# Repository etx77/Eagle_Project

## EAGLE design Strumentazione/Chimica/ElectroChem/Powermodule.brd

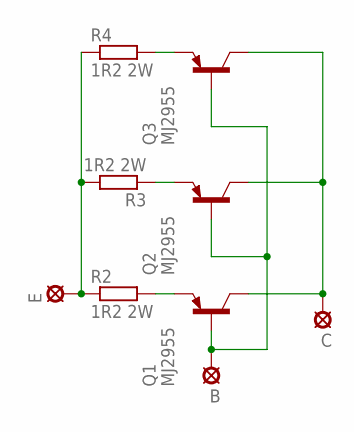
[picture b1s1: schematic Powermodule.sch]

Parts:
B: SE14
C: SE14
E: SE14
Q1, Q2, Q3: MJ2955; TO3
R2, R3, R4: 1R2 2W; 0207/10

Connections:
unnamed: E.MP, R2.1, R3.2, R4.1
unnamed: Q3.E, R4.2
unnamed: Q2.E, R3.1
unnamed: Q1.E, R2.2
unnamed: C.MP, Q1.C, Q1.C/ (C), Q2.C, Q2.C/ (C), Q3.C, Q3.C/ (C)
unnamed: B.MP, Q1.B, Q2.B, Q3.B

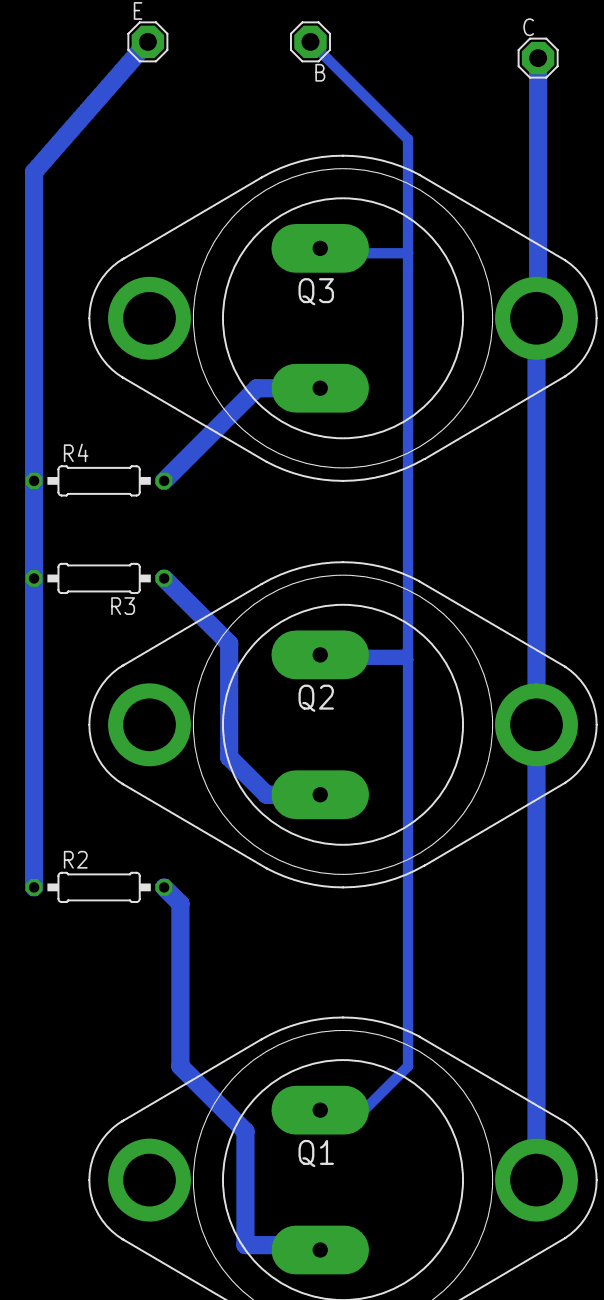
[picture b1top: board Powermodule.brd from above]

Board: 2 copper layers, 9 parts (0 on the bottom side), 6 nets.

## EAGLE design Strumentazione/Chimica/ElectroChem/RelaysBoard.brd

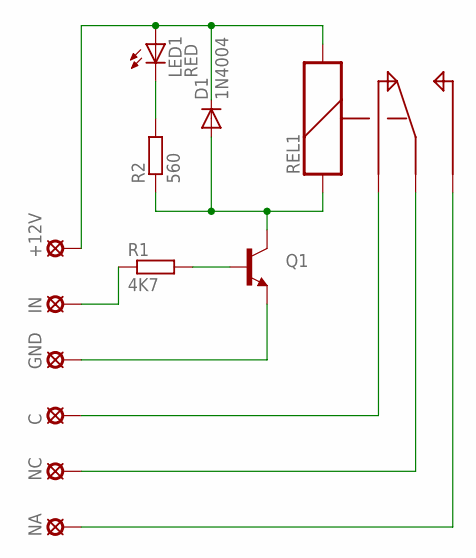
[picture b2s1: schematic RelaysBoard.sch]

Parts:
+12V: LSP10
C: LSP10
D1: 1N4004; DO41-10
GND: LSP10
IN: LSP10
LED1: RED; LED5MM
NA: LSP10
NC: LSP10
Q1: TRANSISTOR_NPNBC547; TO-92-AMMO
R1: 4K7; 0207/12
R2: 560; 0207/10
REL1: REL-5PIN

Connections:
unnamed: +12V.MP, D1.C, LED1.A, REL1.S2
unnamed: D1.A, Q1.1 (C), R2.1, REL1.S1
unnamed: Q1.2 (B), R1.2
unnamed: LED1.K (C), R2.2
unnamed: GND.MP, Q1.3 (E)
unnamed: C.MP, REL1.S
unnamed: NC.MP, REL1.C
unnamed: NA.MP, REL1.O
unnamed: IN.MP, R1.1

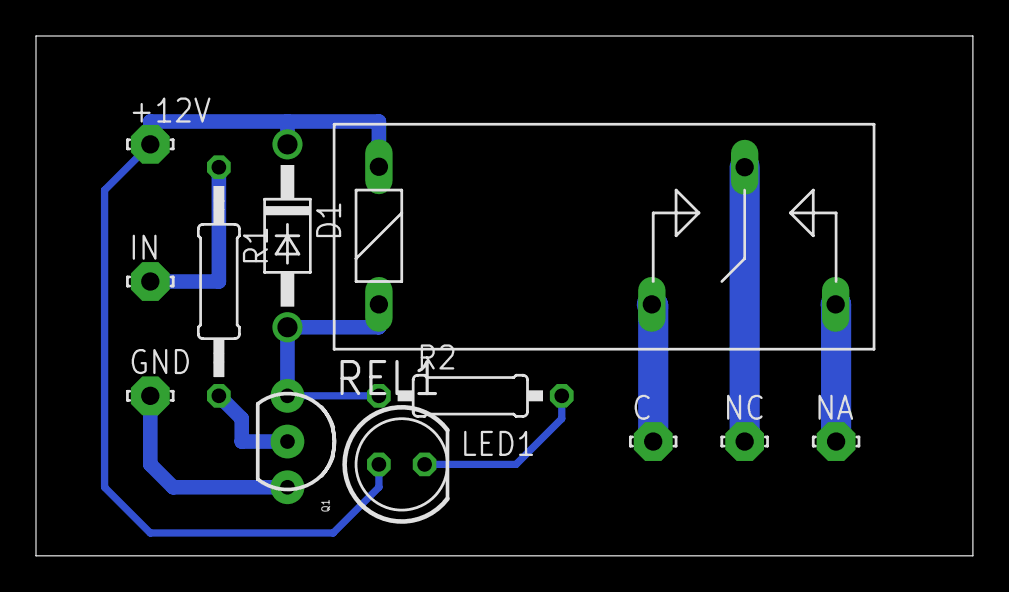
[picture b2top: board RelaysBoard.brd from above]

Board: 2 copper layers, 52.0 x 28.9 mm, 12 parts (0 on the bottom side), 9 nets.

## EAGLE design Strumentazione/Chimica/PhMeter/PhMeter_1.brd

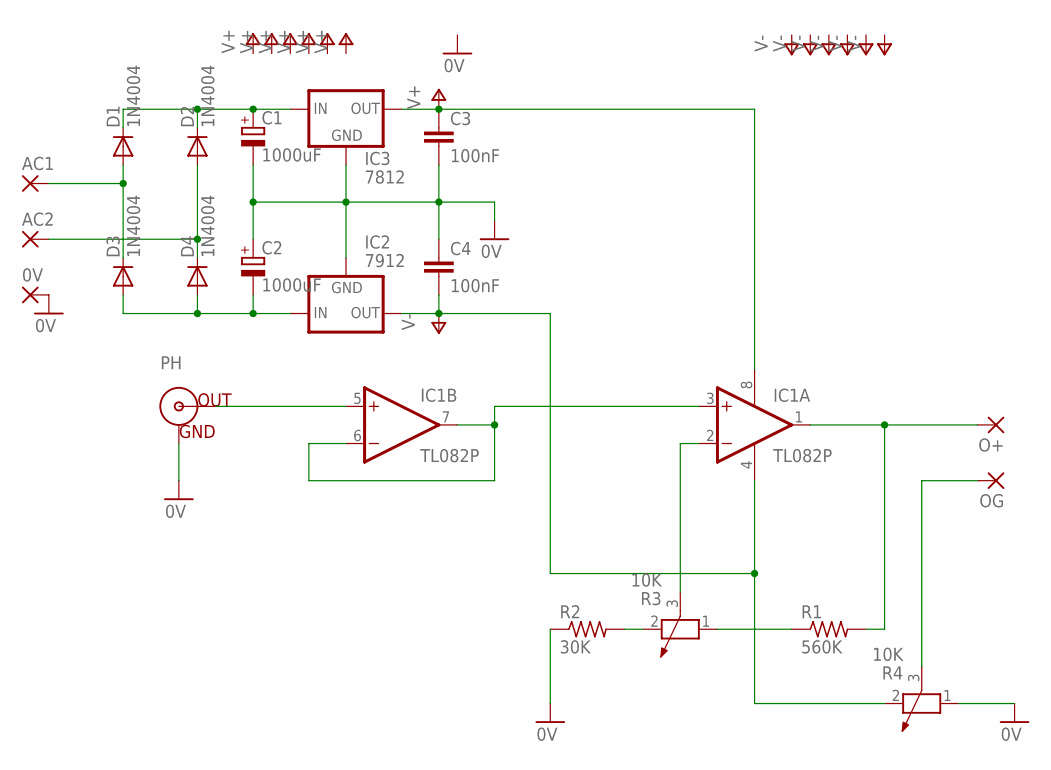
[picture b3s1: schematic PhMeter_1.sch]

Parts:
0V: 1,6/0,8
AC1, AC2: 1,6/0,8
C1, C2: 1000uF; E7,5-18
C3, C4: 100nF; C050-025X075
D1, D2, D3, D4: 1N4004; DO41-10
IC1: TL082P; DIL08
IC2: 7912; 79XXS
IC3: 7812; 78XXS
O+: 1,6/0,8
OG: 1,6/0,8
PH: BNCPTH; BNC
R1: 560K; 0207/10
R2: 30K; 0207/10
R3, R4: 10K; PT-10

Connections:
0V: 0V.1, C1.-, C2.+, C3.2, C4.1, IC2.GND, IC3.GND, PH.GND, R2.1, R4.1
AC1: AC1.1, D1.A, D3.C
unnamed: IC1.3 (+IN), IC1.6 (-IN), IC1.7 (OUT)
unnamed: R2.2, R3.2
unnamed: AC2.1, D2.A, D4.C
unnamed: C1.+, D1.C, D2.C, IC3.IN
unnamed: C2.-, D3.A, D4.A, IC2.IN
unnamed: R1.1, R3.1
unnamed: IC1.1 (OUT), O+.1, R1.2
unnamed: IC1.2 (-IN), R3.3
unnamed: OG.1, R4.3
unnamed: IC1.5 (+IN), PH.S (OUT)
V+: C3.1, IC1.8 (V+), IC3.OUT
V-: C4.2, IC1.4 (V-), IC2.OUT, R4.2

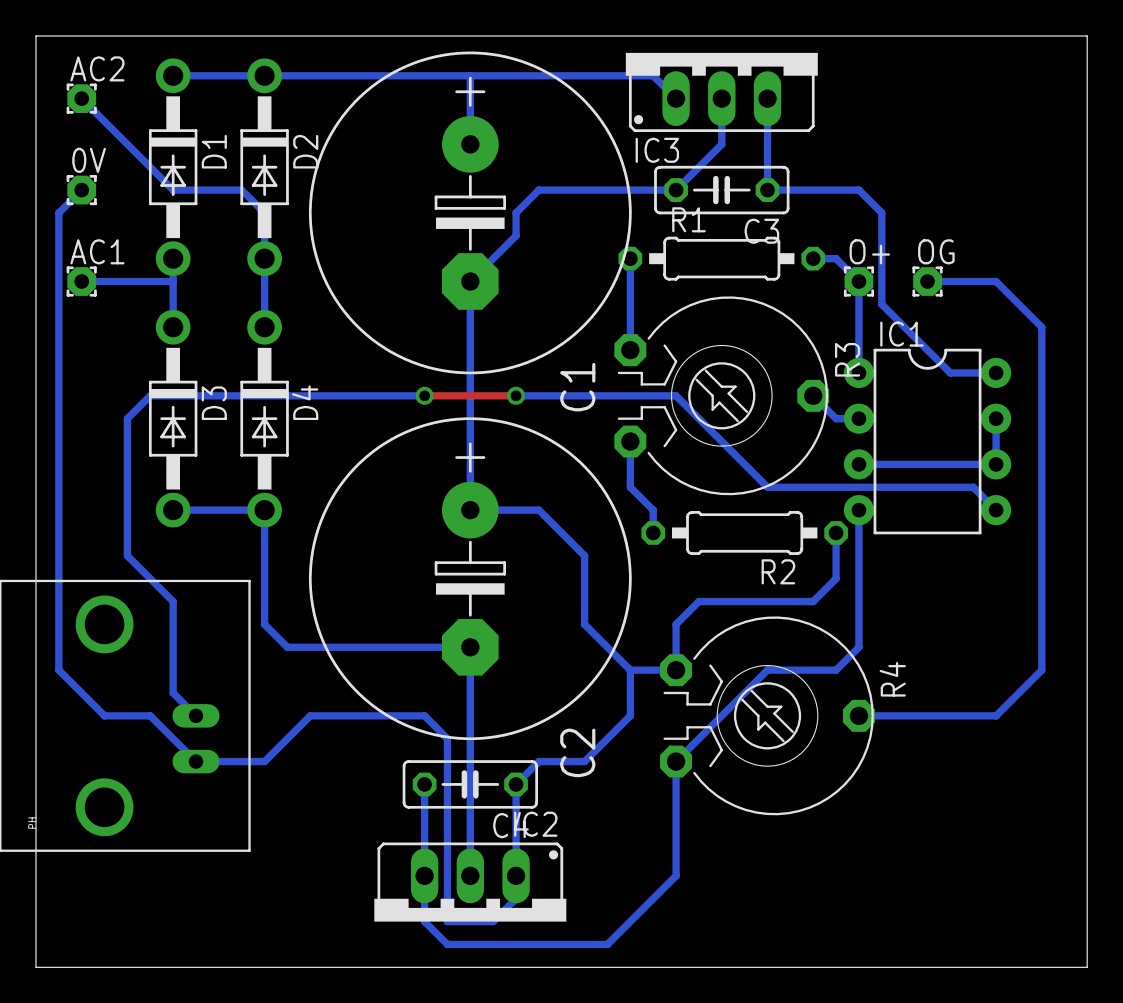
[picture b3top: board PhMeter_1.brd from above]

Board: 2 copper layers, 58.4 x 51.7 mm, 21 parts (0 on the bottom side), 14 nets.

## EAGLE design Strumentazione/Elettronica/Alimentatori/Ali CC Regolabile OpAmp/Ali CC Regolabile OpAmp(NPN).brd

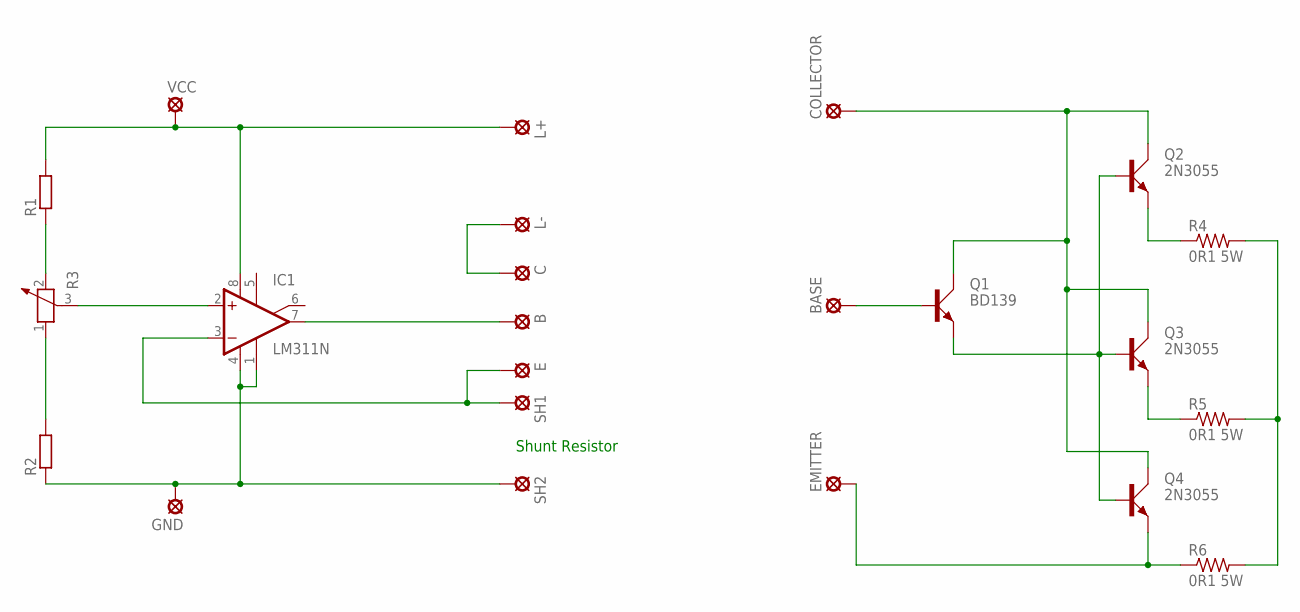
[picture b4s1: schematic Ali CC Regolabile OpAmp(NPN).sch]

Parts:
B: SE14
BASE: SE14
C: SE14
COLLECTOR: SE14
E: SE14
EMITTER: SE14
GND: SE14
IC1: LM311N; DIL08
L+: SE14
L-: SE14
Q1: BD139; TO126AV
Q2, Q3, Q4: 2N3055; TO3A
R1, R2: R-EU_0207/12; 0207/12
R3: POTENTIOMETER_PT-10; PT-10
R4, R5, R6: 0R1 5W; 0617/22
SH1, SH2: SE14
VCC: SE14

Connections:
unnamed: B.MP, IC1.7 (OUT)
unnamed: E.MP, IC1.3 (-IN), SH1.MP
unnamed: C.MP, L-.MP
unnamed: IC1.8 (V+), L+.MP, R1.2, VCC.MP
unnamed: R1.1, R3.2
unnamed: R2.2, R3.1
unnamed: IC1.2 (+IN), R3.3
unnamed: GND.MP, IC1.1 (GND), IC1.4 (V-), R2.1, SH2.MP
unnamed: Q3.E, R5.1
unnamed: EMITTER.MP, Q4.E, R6.1
unnamed: COLLECTOR.MP, Q1.C, Q2.C, Q2.C1 (C), Q3.C, Q3.C1 (C), Q4.C, Q4.C1 (C)
unnamed: Q2.E, R4.1
unnamed: R4.2, R5.2, R6.2
unnamed: Q1.E, Q2.B, Q3.B, Q4.B
unnamed: BASE.MP, Q1.B

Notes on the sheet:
Shunt Resistor

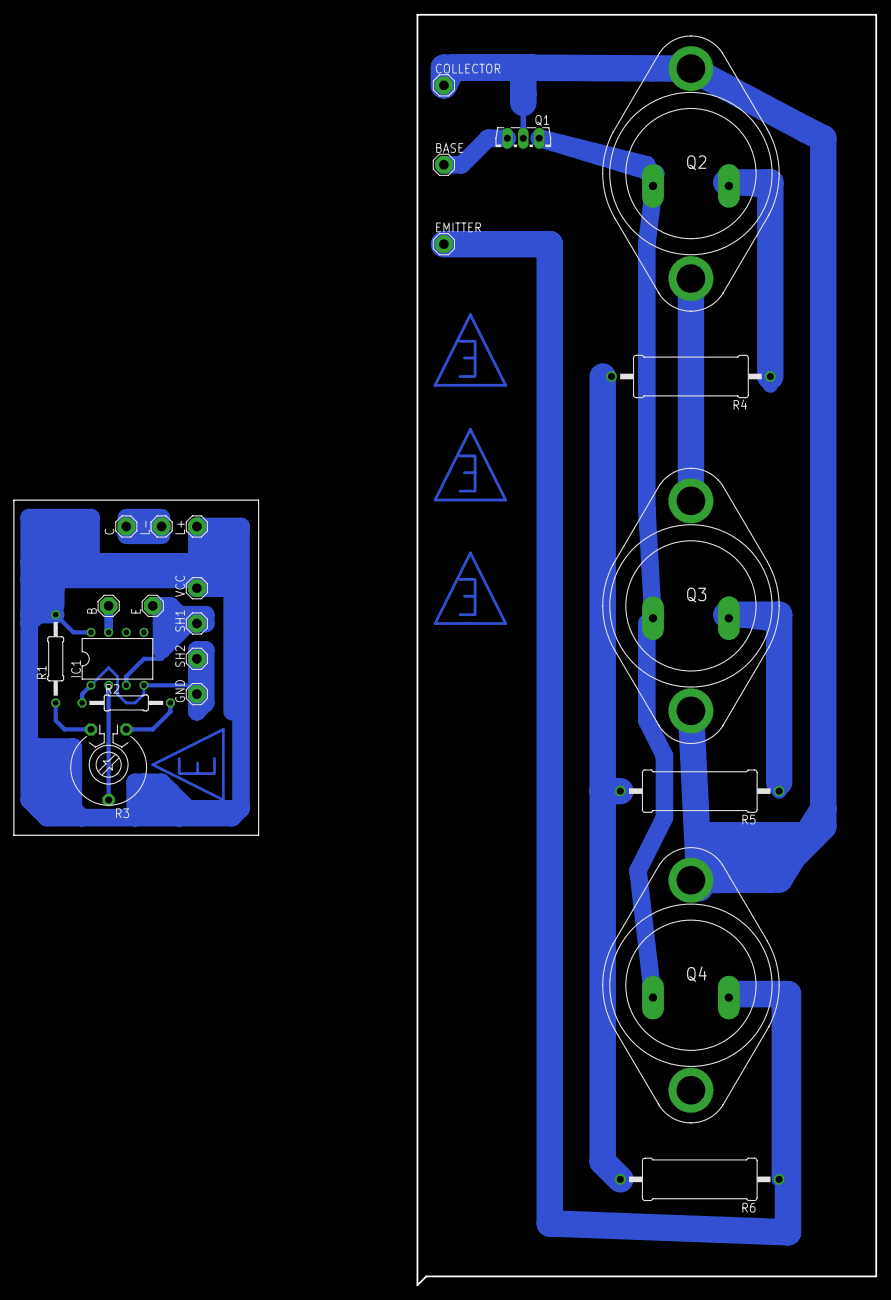
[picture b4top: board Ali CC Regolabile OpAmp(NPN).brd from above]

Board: 2 copper layers, 124.1 x 182.9 mm, 27 parts (0 on the bottom side), 15 nets.

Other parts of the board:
U$1, U$2, U$3, U$4: LOGO

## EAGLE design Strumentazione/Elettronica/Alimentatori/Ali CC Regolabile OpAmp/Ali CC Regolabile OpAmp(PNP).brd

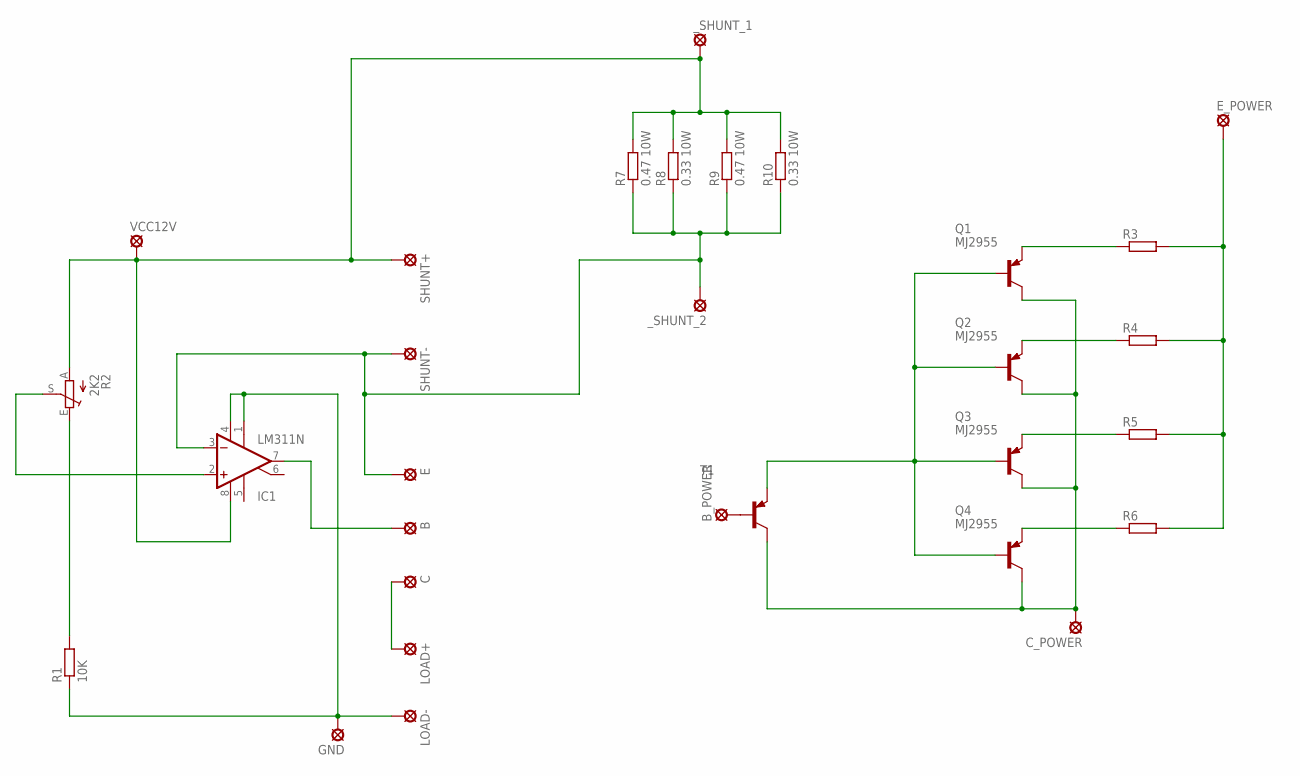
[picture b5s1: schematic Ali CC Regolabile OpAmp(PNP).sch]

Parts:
B: SE14
B_POWER: LSP10
C: SE14
C_POWER: LSP10
E: SE14
E_POWER: LSP10
GND: SE14
IC1: LM311N; DIL08
LOAD+: SE14
LOAD-: SE14
Q1, Q2, Q3, Q4: MJ2955; TO3
R1: 10K; 0207/15
R2: 2K2; CIP20C-6MM
R3, R4, R5, R6: R-EU_VTA53; VTA53
R7, R9: 0.47 10W; VTA53
R8, R10: 0.33 10W; VTA53
SHUNT+: SE14
SHUNT-: SE14
T1: BC558A-PNP-TO92-EBC; TO92-EBC
VCC12V: SE14
_SHUNT_1, _SHUNT_2: LSP10

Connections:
unnamed: E.MP, IC1.3 (-IN), R7.1, R8.1, R9.1, R10.1, SHUNT-.MP, _SHUNT_2.MP
unnamed: B.MP, IC1.7 (OUT)
unnamed: C.MP, LOAD+.MP
unnamed: GND.MP, IC1.1 (GND), IC1.4 (V-), LOAD-.MP, R1.1
unnamed: R1.2, R2.E
unnamed: Q1.E, R3.1
unnamed: IC1.2 (+IN), R2.S
unnamed: Q2.E, R4.1
unnamed: Q3.E, R5.1
unnamed: Q4.E, R6.1
unnamed: E_POWER.MP, R3.2, R4.2, R5.2, R6.2
unnamed: C_POWER.MP, Q1.C, Q1.C/ (C), Q2.C, Q2.C/ (C), Q3.C, Q3.C/ (C), Q4.C, Q4.C/ (C), T1.C
unnamed: Q1.B, Q2.B, Q3.B, Q4.B, T1.E
unnamed: B_POWER.MP, T1.B
unnamed: IC1.8 (V+), R2.A, R7.2, R8.2, R9.2, R10.2, SHUNT+.MP, VCC12V.MP, _SHUNT_1.MP

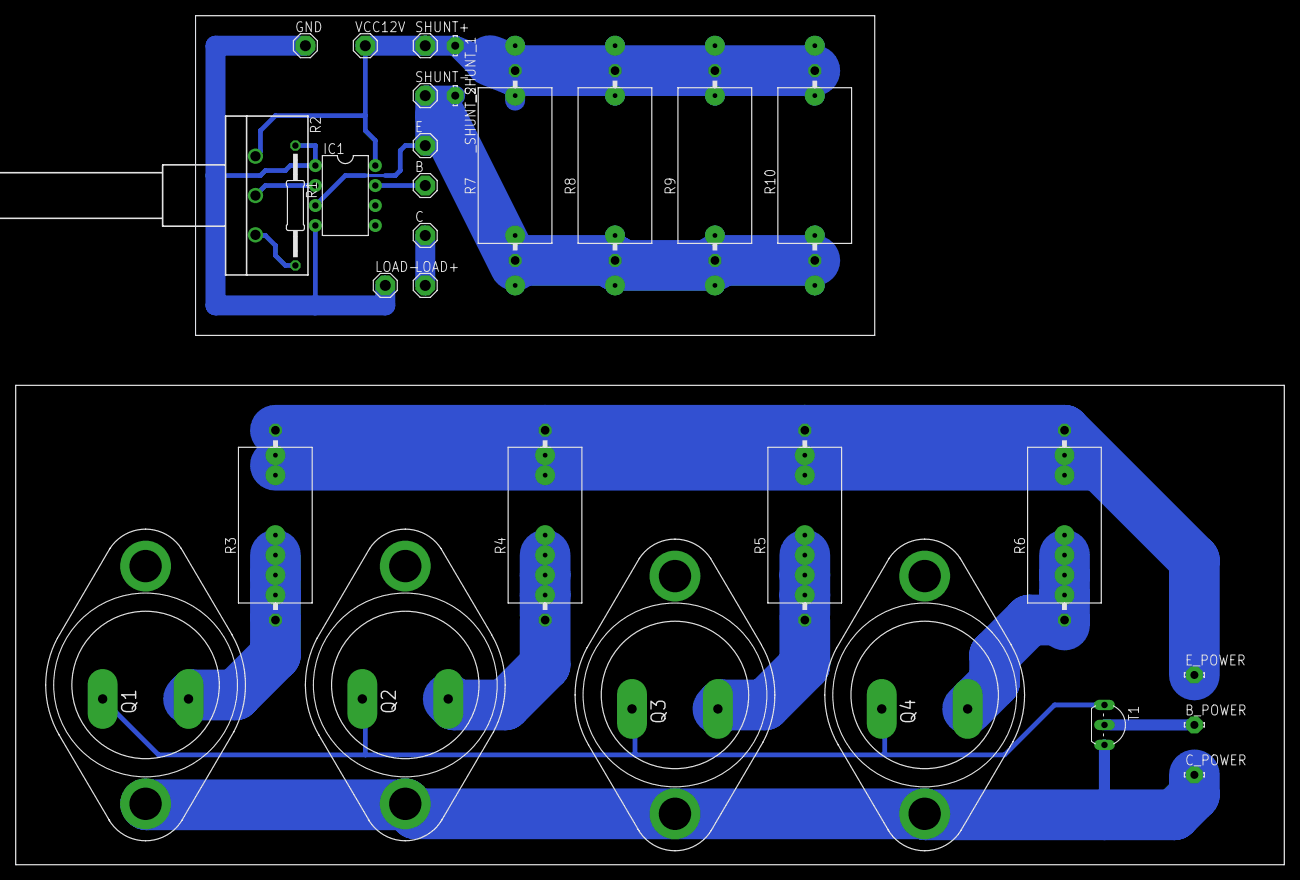
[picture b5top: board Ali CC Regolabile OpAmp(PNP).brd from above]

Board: 2 copper layers, 161.3 x 108.0 mm, 30 parts (0 on the bottom side), 15 nets.

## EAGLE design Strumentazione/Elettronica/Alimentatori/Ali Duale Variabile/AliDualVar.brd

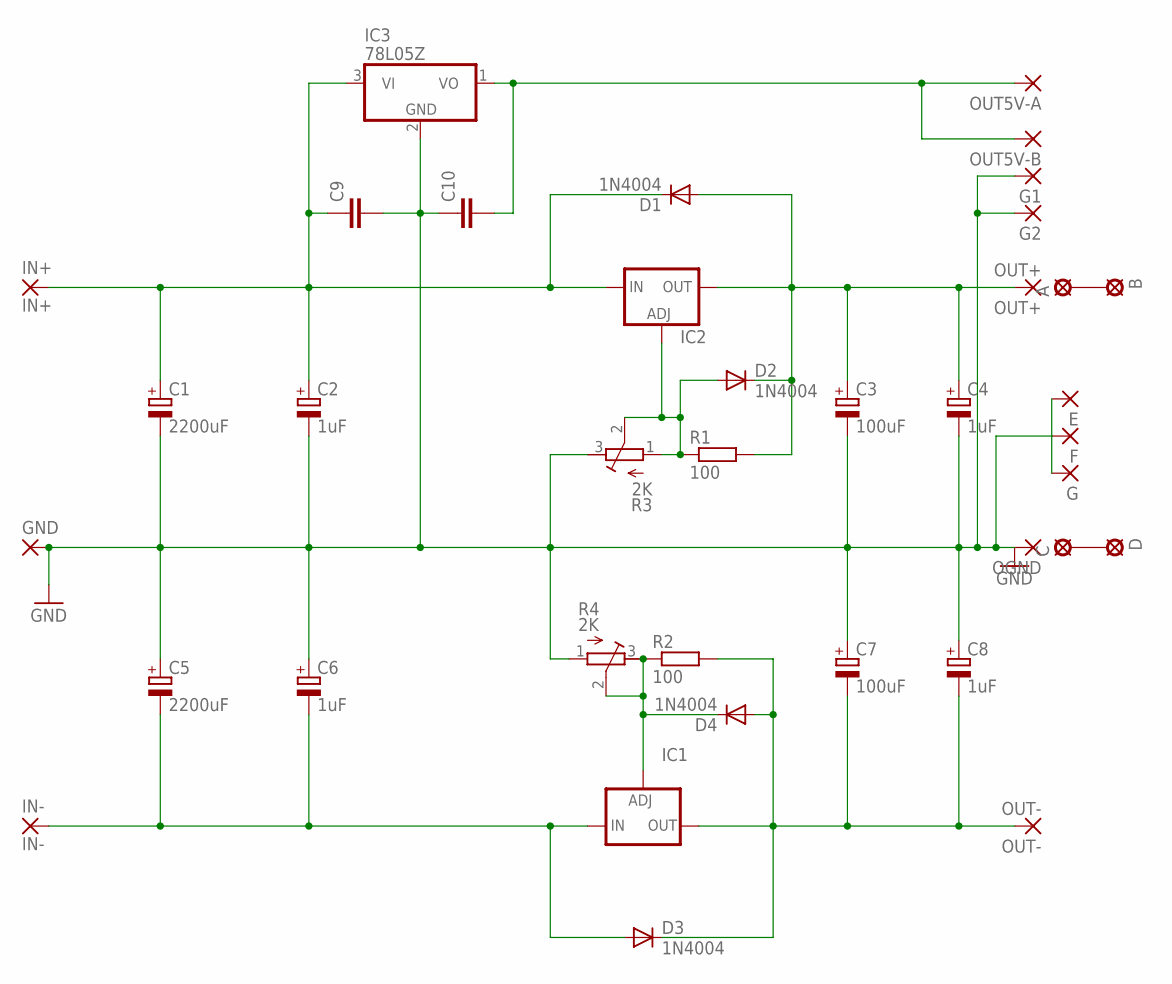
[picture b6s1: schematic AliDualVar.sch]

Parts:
A: MCS10B
B: MCS10B
C: MCS10B
C1, C5: 2200uF; EB35D
C2, C4, C6, C8: 1uF; E5-13
C3, C7: 100uF; E5-13
C9, C10: C-EU025-024X044; C025-024X044
D: MCS10B
D1, D2, D3, D4: 1N4004; DO41-10
E: 3,81/1,4
F: 3,81/1,4
G, G1, G2: 3,81/1,4
GND: 3,81/1,4
IC1: LM337TL; 337TL
IC2: LM317TL; 317TL
IC3: 78L05Z; TO92
IN+: IN+; 3,81/1,4
IN-: IN-; 3,81/1,4
OGND: 3,81/1,4
OUT5V-A, OUT5V-B: 3,81/1,4
OUT+: OUT+; 3,81/1,4
OUT-: OUT-; 3,81/1,4
R1, R2: 100; 0207/7
R3, R4: 2K; RTRIM3339P

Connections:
GND: C1.-, C2.-, C3.-, C4.-, C5.+, C6.+, C7.+, C8.+, C9.2, C10.1, E.1, F.1, G.1, G1.1, G2.1, GND.1, IC3.2 (GND), OGND.1, R3.3 (E), R4.1 (A)
unnamed: C3.+, C4.+, D1.A, D2.C, IC2.2 (OUT), OUT+.1, R1.2
unnamed: A.MP, B.MP
unnamed: C.MP, D.MP
unnamed: D2.A, IC2.1 (ADJ), R1.1, R3.1 (A), R3.2 (S)
unnamed: D4.C, IC1.1 (ADJ), R2.1, R4.2 (S), R4.3 (E)
unnamed: C7.-, C8.-, D3.C, D4.A, IC1.3 (OUT), OUT-.1, R2.2
unnamed: C5.-, C6.-, D3.A, IC1.2 (IN), IN-.1
unnamed: C10.2, IC3.1 (VO), OUT5V-A.1, OUT5V-B.1
unnamed: C1.+, C2.+, C9.1, D1.C, IC2.3 (IN), IC3.3 (VI), IN+.1

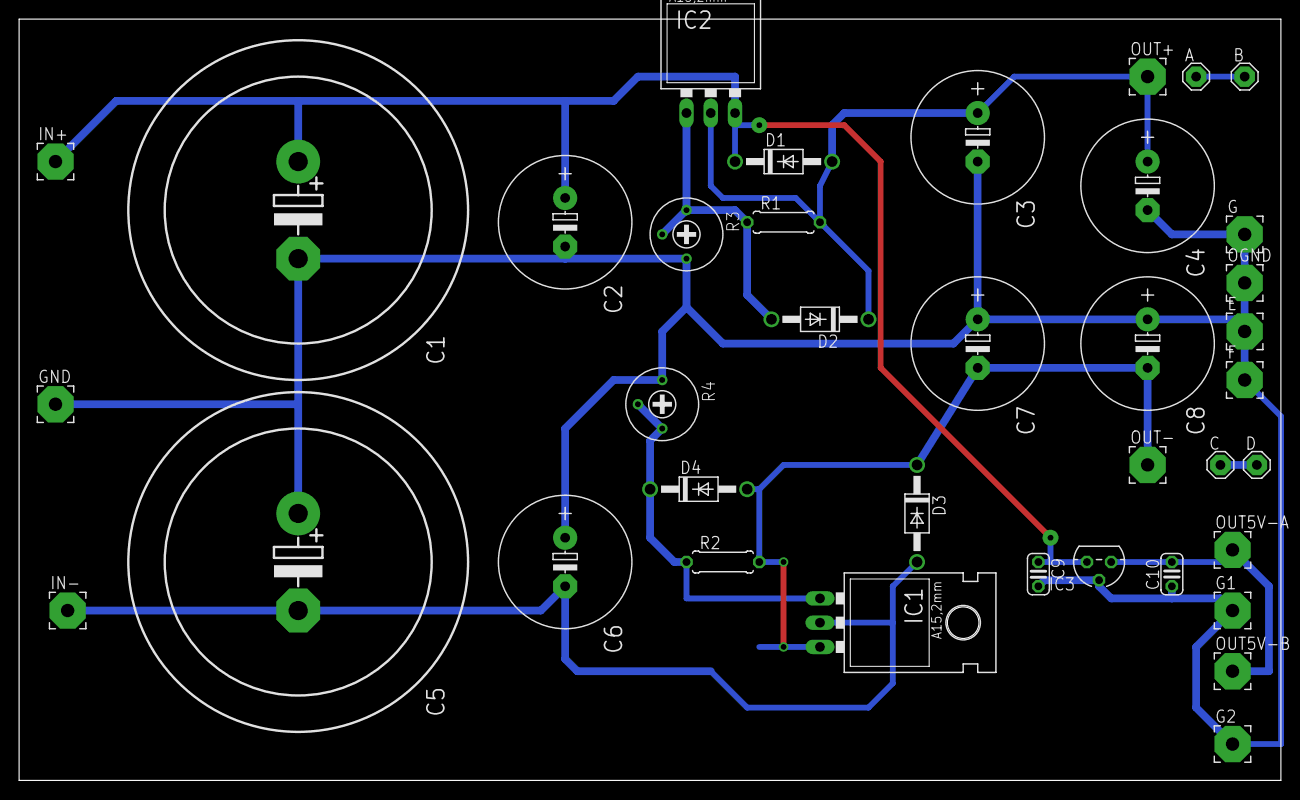
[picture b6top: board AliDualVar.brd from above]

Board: 2 copper layers, 132.1 x 79.7 mm, 38 parts (0 on the bottom side), 10 nets.

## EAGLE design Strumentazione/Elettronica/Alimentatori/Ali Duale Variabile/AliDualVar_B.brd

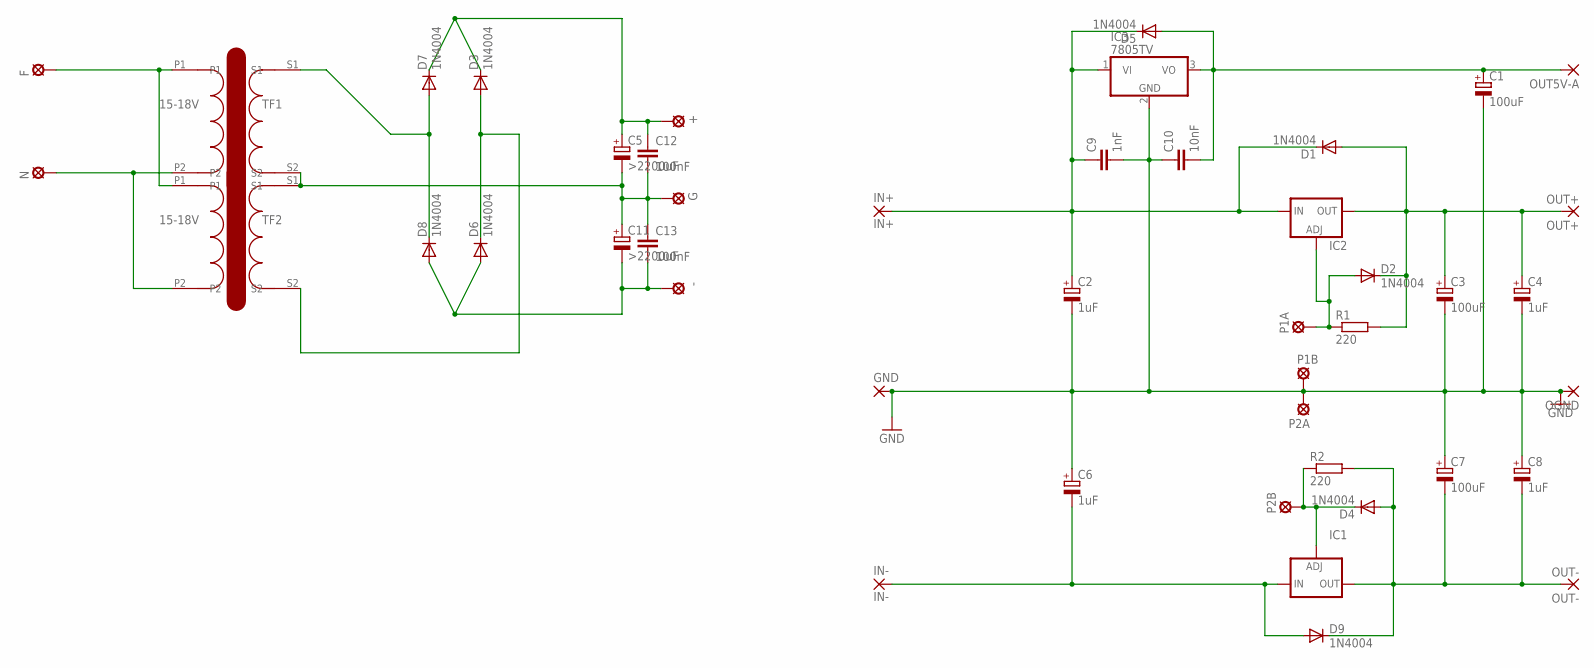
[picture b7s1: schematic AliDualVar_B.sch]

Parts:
+: LSP10
-: LSP10
C1, C3, C7: 100uF; E5-13
C2, C4, C6, C8: 1uF; E5-13
C5, C11: >2200uF; E7,5-16
C9: 1nF; C025-024X044
C10: 10nF; C025-024X044
C12, C13: 100nF; C050-035X075
D1, D2, D3, D4, D5, D6, D7, D8, D9: 1N4004; DO41-10
F: LSP10
G: LSP10
GND: 3,81/1,4
IC1: LM337TS; 337TS
IC2: LM317TS; 317TS
IC3: 7805TV; TO220V
IN+: IN+; 3,81/1,4
IN-: IN-; 3,81/1,4
N: LSP10
OGND: 3,81/1,4
OUT5V-A: 3,81/1,4
OUT+: OUT+; 3,81/1,4
OUT-: OUT-; 3,81/1,4
P1A, P1B, P2A, P2B: LSP10
R1, R2: 220; 0207/7
TF1, TF2: 15-18V; TRASFORMATORE_1_A

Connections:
GND: C1.-, C2.-, C3.-, C4.-, C6.+, C7.+, C8.+, C9.2, C10.1, GND.1, IC3.2 (GND), OGND.1, P1B.MP, P2A.MP
unnamed: C7.-, C8.-, D4.A, D9.C, IC1.3 (OUT), OUT-.1, R2.2
unnamed: C3.+, C4.+, D1.A, D2.C, IC2.2 (OUT), OUT+.1, R1.2
unnamed: F.MP, TF1.P1, TF2.P1
unnamed: C1.+, C10.2, D5.A, IC3.3 (VO), OUT5V-A.1
unnamed: D2.A, IC2.1 (ADJ), P1A.MP, R1.1
unnamed: D4.C, IC1.1 (ADJ), P2B.MP, R2.1
unnamed: D7.A, D8.C, TF1.S1
unnamed: C6.-, D9.A, IC1.2 (IN), IN-.1
unnamed: D3.A, D6.C, TF2.S2
unnamed: C2.+, C9.1, D1.C, D5.C, IC2.3 (IN), IC3.1 (VI), IN+.1
unnamed: +.MP, C5.+, C12.1, D3.C, D7.C
unnamed: N.MP, TF1.P2, TF2.P2
unnamed: C5.-, C11.+, C12.2, C13.1, G.MP, TF1.S2, TF2.S1
unnamed: -.MP, C11.-, C13.2, D6.A, D8.A

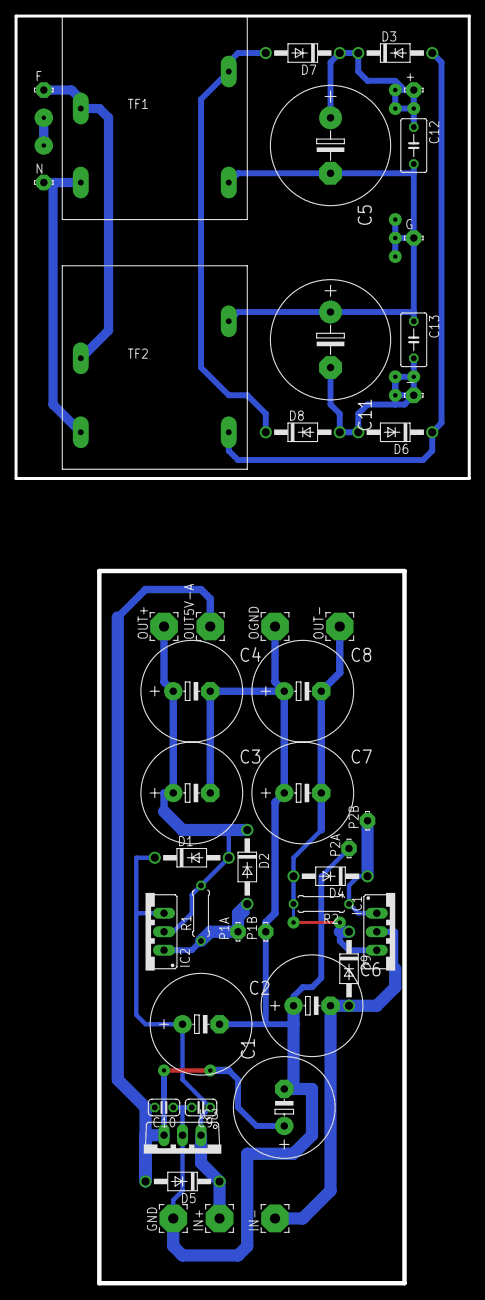
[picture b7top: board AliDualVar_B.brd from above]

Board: 2 copper layers, 62.2 x 174.0 mm, 45 parts (0 on the bottom side), 15 nets.

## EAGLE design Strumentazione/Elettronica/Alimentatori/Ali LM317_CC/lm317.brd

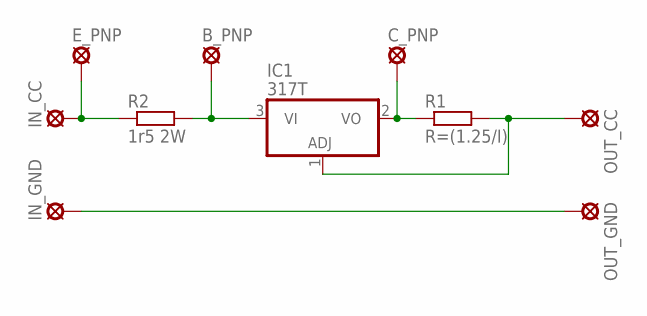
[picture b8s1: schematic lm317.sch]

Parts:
B_PNP: SE14
C_PNP: SE14
E_PNP: SE14
IC1: 317T; TO220H
IN_CC: SE14
IN_GND: SE14
OUT_CC: SE14
OUT_GND: SE14
R1: R=(1.25/I); 0617/22
R2: 1r5 2W; 0617/22

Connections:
unnamed: E_PNP.MP, IN_CC.MP, R2.1
unnamed: B_PNP.MP, IC1.3 (VI), R2.2
unnamed: C_PNP.MP, IC1.2 (VO), R1.1
unnamed: IC1.1 (ADJ), OUT_CC.MP, R1.2
unnamed: IN_GND.MP, OUT_GND.MP

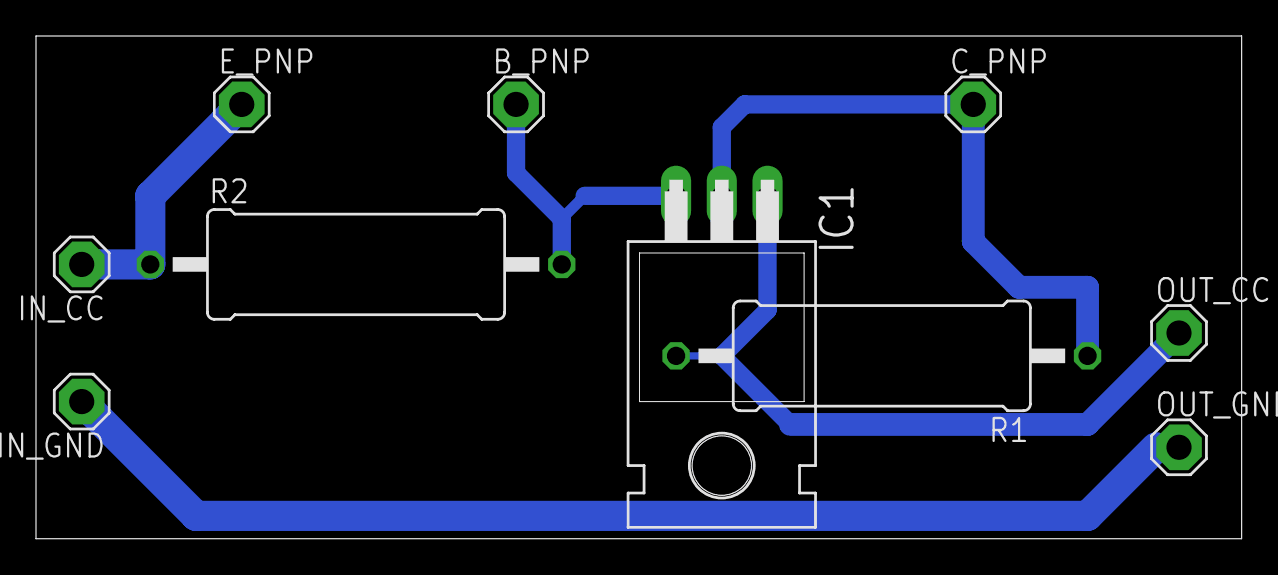
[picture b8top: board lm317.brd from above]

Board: 2 copper layers, 67.0 x 27.9 mm, 10 parts (0 on the bottom side), 5 nets.

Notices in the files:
parts and their libraries:
SparkFun-DiscreteSemi: Licensing: Creative Commons ShareAlike 4.0 International - https://creativecommons.org/licenses/by-sa/4.0
